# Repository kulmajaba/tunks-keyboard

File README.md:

# Tunks keyboards
> Formerly: The project that will someday be the ultimate command center upgrade

This repo contains the Tunks series keyboard schematics, born as an experiment to make a macro keyboard for editing, gaming and testing mechanical switches.

## Roadmap

Companion app: a combination of hardware and software allowing the user to control programs like Discord and OBS as well as receive visual feedback in the form of "tally lights".
Keyboard shortcuts are fragile and unpredictable, and software like AutoHotKey is considered cheating software by a lot of anti-cheat utilities, regardless of what you do with it.

**Resources**

- Discord: mute and deaf states, and setting the states instead of toggling: https://discordapp.com/developers/docs/game-sdk/discord-voice
- OBS: See which outputs are in use in the current scene (we're interested in camera, display capture and microphone), switch between scenes: https://obsproject.com/docs/
- QMK with SysEx Midi messages: https://beta.docs.qmk.fm/developing-qmk/qmk-internals-in-progress/internals_midi_device
- Keyboard PCB guide: https://wiki.ai03.com/books/pcb-design

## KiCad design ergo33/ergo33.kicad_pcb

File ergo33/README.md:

# Ergo33

A left-hand keypad with a rotary encoder for gaming, video editing, macros etc.
* 33 keys plus rotary encoder with press switch
* Kailh hot-swap sockets
* Ergonomic layout (straight columns, staggered rows)
* LED underglow and the option to add an ergo33-led-board (or any other similar external PCB) for state indicators etc.

## Notes

* The WS2812B LEDs can be configured in three different ways and you may need to change hardware or firmware config:
  * Both underglow and external board in use: Bridge the solder jumper JP1 pads 1 and 2
  * Underglow in use, no external board: reduce the number of LEDs in firmware config
  * External board in use, no underglow: Bridge the solder jumper JP1 pads 2 and 3, reduce the number of LEDs in firmware config
* Spark suppression cap C19 may be omitted or resized, may affect bootloader activation time
* The highest component on the underside of the PCB is the USB-C connector at 3,15mm
* The rotary encoder position is sized for a 30mm knob

## BOM

| Component | Value | Quantity | Example | Notes |
| --------- | ----- | -------- | ------- | ----- |
| ATmega32U4-AU TQFP-44 |  | 1 |  |  |
| Capacitor 0805 | 16pF | 2 |  | Crystal caps, size according to the crystal used |
| Capacitor 0805 | 510pF | 1 |  | Spark suppression capacitor C19 |
| Capacitor 0805 | 0.1uF | 19 |  |  |
| Capacitor 0805 | 1uF | 1 |  |  |
| Capacitor 0805 | 10uF | 2 |  |  |
| Crystal 3.2x2.5mm | 16MHz | 1 | DSX321G |  |
| Diode SOD-123 |  | 34 | 1N4148 |  |
| Fuse 1206 | 500mA | 1 | Littelfuse 1206L050/15 |  |
| Kailh Hot-swap Socket |  | 33 |  |  |
| LED WS2812B |  | 14 |  |  |
| Pin header 2.54mmx3 |  | 1 |  |  |
| Resistor 0805 | 22Ω | 2 |  |  |
| Resistor 0805 | 5.1kΩ | 2 |  |  |
| Resistor 0805 | 10kΩ | 2 |  |  |
| Rotary encoder EC11 |  | 1 |  |  |
| Switch 4x4mm SMD |  | 1 |  |  |
| USB-C 16 pin |  | 1 | HRO-TYPE-C-31-M-12 |  |
| USBLC6-2SC6 SOT-23-6 |  | 1 |  |  |
| M2 Mounting hardware |  | 12 |  |  |
| 30mm Encoder knob |  | 1 |  |  |

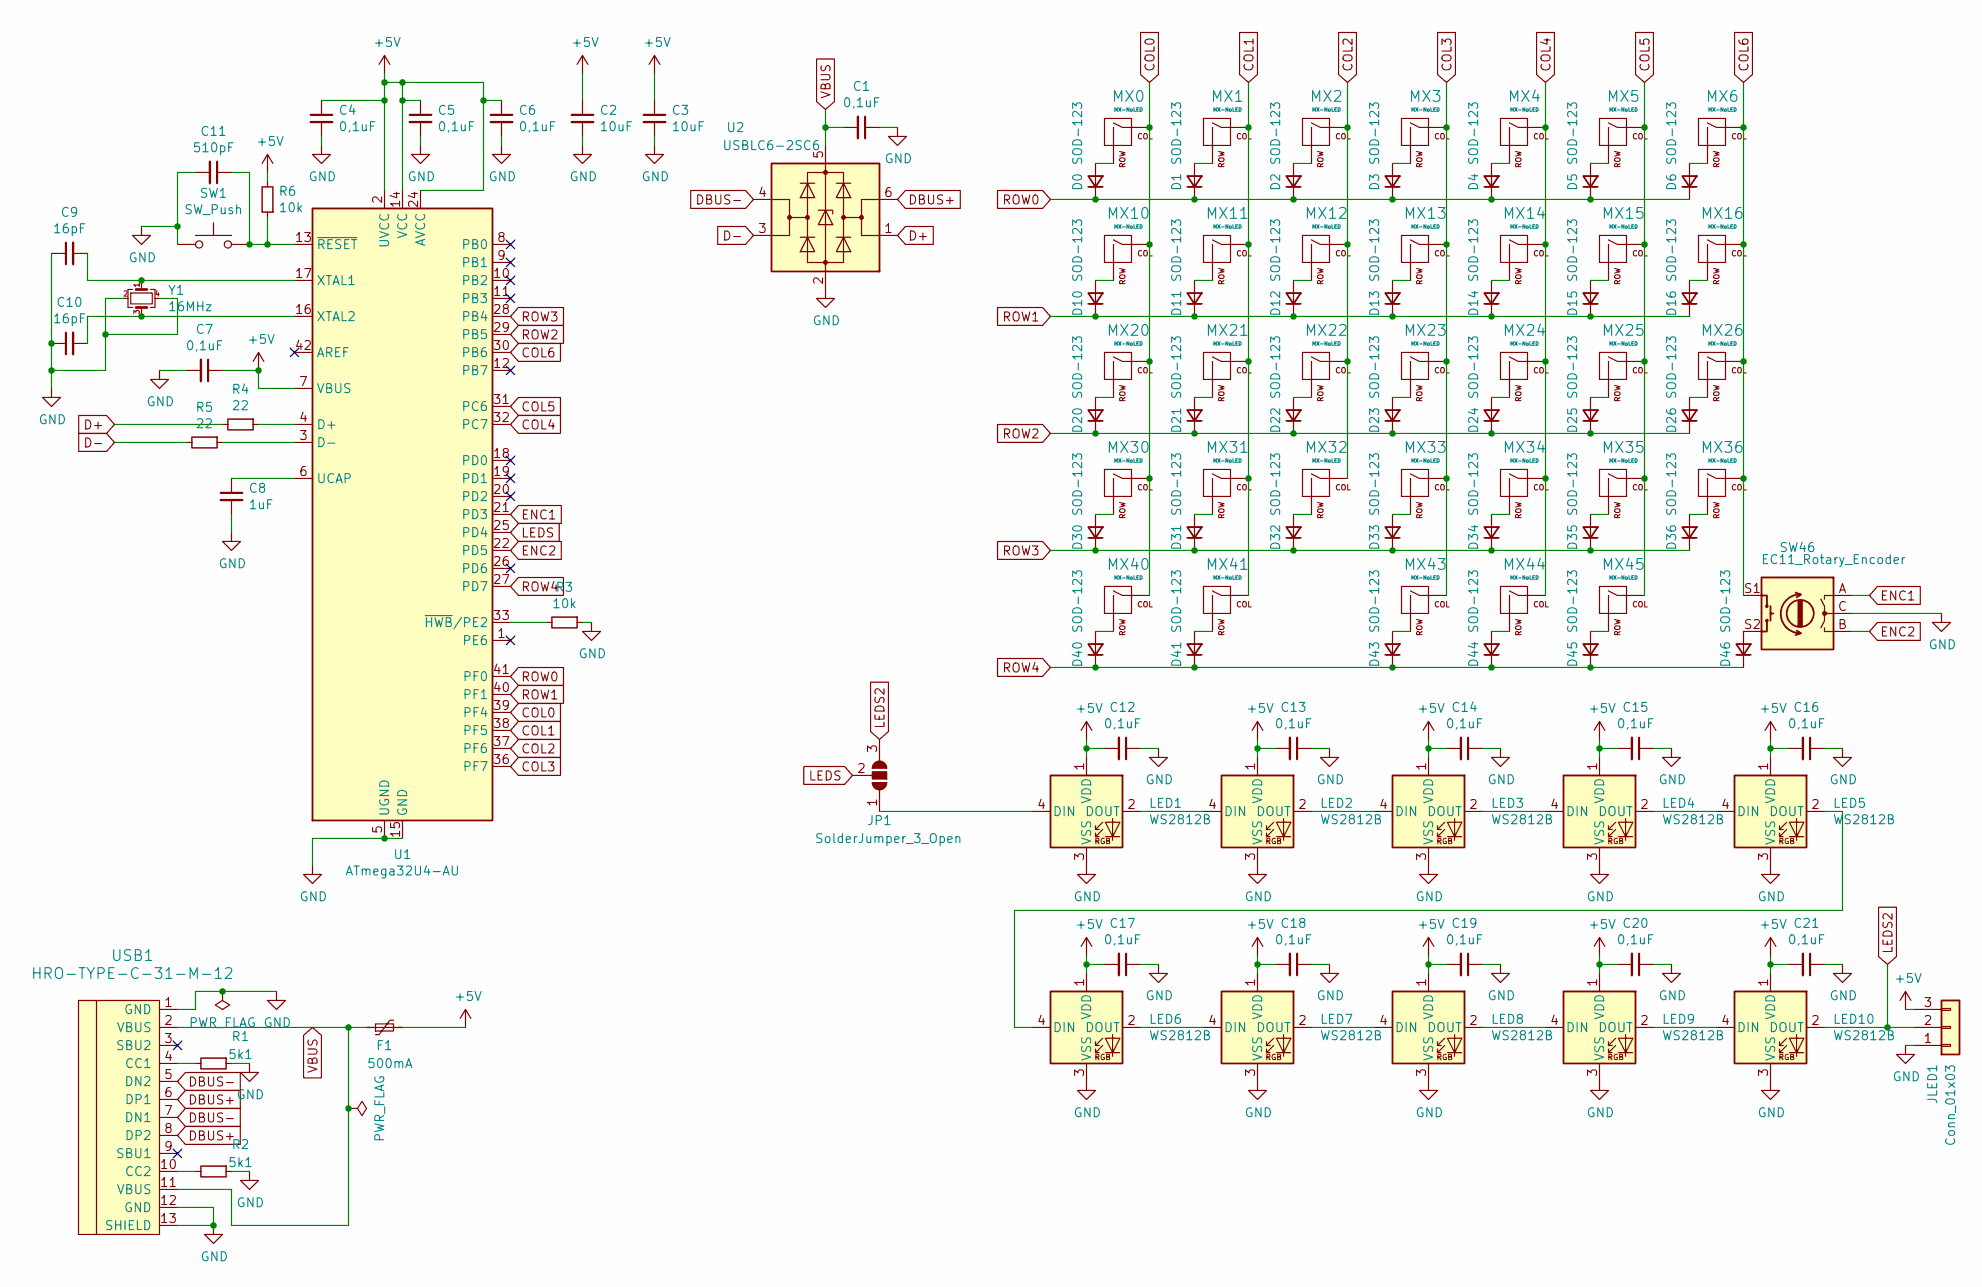
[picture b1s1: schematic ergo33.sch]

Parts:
C1, C4, C5, C6, C7, C12, C13, C14, C15, C16, C17, C18, C19, C20, C21: 0,1uF; C_0805_2012Metric_Pad1.15x1.40mm_HandSolder
C2, C3: 10uF; C_0805_2012Metric_Pad1.15x1.40mm_HandSolder
C8: 1uF; C_0805_2012Metric_Pad1.15x1.40mm_HandSolder
C9, C10: 16pF; C_0805_2012Metric_Pad1.15x1.40mm_HandSolder
C11: 510pF; C_0805_2012Metric_Pad1.15x1.40mm_HandSolder
D0, D1, D2, D3, D4, D5, D6, D10, D11, D12, D13, D14, D15, D16, D20, D21, D22, D23, D24, D25, D26, D30, D31, D32, D33, D34, D35, D36, D40, D41, D43, D44, D45, D46: SOD-123; D_SOD-123
F1: 500mA; Fuse_1206_3216Metric_Pad1.42x1.75mm_HandSolder
JLED1: Conn_01x03; PinHeader_1x03_P2.54mm_Vertical
JP1: SolderJumper_3_Open; SolderJumper-3_P1.3mm_Open_Pad1.0x1.5mm_NumberLabels
LED1, LED2, LED3, LED4, LED5, LED6, LED7, LED8, LED9, LED10: WS2812B; LED_WS2812B_PLCC4_5.0x5.0mm_P3.2mm
MX0, MX1, MX2, MX3, MX4, MX5, MX6, MX10, MX11, MX12, MX13, MX14, MX15, MX16, MX20, MX21, MX22, MX23, MX24, MX25, MX26, MX30, MX31, MX32, MX33, MX34, MX35, MX36, MX40, MX41, MX43, MX44, MX45: MX-NoLED; MXOnly-1U-Hotswap
R1, R2: 5k1; R_0805_2012Metric_Pad1.15x1.40mm_HandSolder
R3, R6: 10k; R_0805_2012Metric_Pad1.15x1.40mm_HandSolder
R4, R5: 22; R_0805_2012Metric_Pad1.15x1.40mm_HandSolder
SW1: SW_Push; SKQG-1155865
SW46: EC11_Rotary_Encoder; RotaryEncoder_Alps_EC11E-Switch_Vertical_H20mm
U1: ATmega32U4-AU; TQFP-44_10x10mm_P0.8mm
U2: USBLC6-2SC6; SOT-23-6_Handsoldering
USB1: HRO-TYPE-C-31-M-12; HRO-TYPE-C-31-M-12-HandSoldering
Y1: 16MHz; Crystal_SMD_3225-4Pin_3.2x2.5mm_HandSoldering

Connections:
+5V: C2.1, C3.1, C4.1, C5.1, C6.1, C7.1, C12.2, C13.2, C14.2, C15.2, C16.2, C17.2, C18.2, C19.2, C20.2, C21.2, F1.2, JLED1.3, LED1.1 (VDD), LED2.1 (VDD), LED3.1 (VDD), LED4.1 (VDD), LED5.1 (VDD), LED6.1 (VDD), LED7.1 (VDD), LED8.1 (VDD), LED9.1 (VDD), LED10.1 (VDD), R6.2, U1.2 (UVCC), U1.7 (VBUS), U1.14 (VCC), U1.24 (AVCC), U1.34 (VCC), U1.44 (AVCC)
COL0: MX0.1 (COL), MX10.1 (COL), MX20.1 (COL), MX30.1 (COL), MX40.1 (COL), U1.39 (PF4)
COL1: MX1.1 (COL), MX11.1 (COL), MX21.1 (COL), MX31.1 (COL), MX41.1 (COL), U1.38 (PF5)
COL2: MX2.1 (COL), MX12.1 (COL), MX22.1 (COL), MX32.1 (COL), U1.37 (PF6)
COL3: MX3.1 (COL), MX13.1 (COL), MX23.1 (COL), MX33.1 (COL), MX43.1 (COL), U1.36 (PF7)
COL4: MX4.1 (COL), MX14.1 (COL), MX24.1 (COL), MX34.1 (COL), MX44.1 (COL), U1.32 (PC7)
COL5: MX5.1 (COL), MX15.1 (COL), MX25.1 (COL), MX35.1 (COL), MX45.1 (COL), U1.31 (PC6)
COL6: MX6.1 (COL), MX16.1 (COL), MX26.1 (COL), MX36.1 (COL), SW46.S1, U1.30 (PB6)
D+: R4.2, U2.1 (I/O1)
D-: R5.2, U2.3 (I/O2)
DBUS+: U2.6 (I/O1), USB1.6 (DP1), USB1.8 (DP2)
DBUS-: U2.4 (I/O2), USB1.5 (DN2), USB1.7 (DN1)
ENC1: SW46.A, U1.21 (PD3)
ENC2: SW46.B, U1.22 (PD5)
GND: C1.1, C2.2, C3.2, C4.2, C5.2, C6.2, C7.2, C8.2, C9.1, C10.1, C11.2, C12.1, C13.1, C14.1, C15.1, C16.1, C17.1, C18.1, C19.1, C20.1, C21.1, JLED1.1, LED1.3 (VSS), LED2.3 (VSS), LED3.3 (VSS), LED4.3 (VSS), LED5.3 (VSS), LED6.3 (VSS), LED7.3 (VSS), LED8.3 (VSS), LED9.3 (VSS), LED10.3 (VSS), R1.1, R2.1, R3.1, SW1.1, SW46.C, U1.5 (UGND), U1.15 (GND), U1.23 (GND), U1.35 (GND), U1.43 (GND), U2.2 (GND), USB1.1 (GND), USB1.12 (GND), USB1.13 (SHIELD), Y1.2, Y1.4
LEDS: JP1.2 (C), U1.25 (PD4)
LEDS2: JLED1.2, JP1.3 (B), LED10.2 (DOUT)
unnamed: C8.1, U1.6 (UCAP)
unnamed: C9.2, U1.17 (XTAL1), Y1.1
unnamed: C10.2, U1.16 (XTAL2), Y1.3
unnamed: C11.1, R6.1, SW1.2, U1.13 (~RESET)
unnamed: D0.2 (A), MX0.2 (ROW)
unnamed: D1.2 (A), MX1.2 (ROW)
unnamed: D2.2 (A), MX2.2 (ROW)
unnamed: D3.2 (A), MX3.2 (ROW)
unnamed: D4.2 (A), MX4.2 (ROW)
unnamed: D5.2 (A), MX5.2 (ROW)
unnamed: D6.2 (A), MX6.2 (ROW)
unnamed: D10.2 (A), MX10.2 (ROW)
unnamed: D11.2 (A), MX11.2 (ROW)
unnamed: D12.2 (A), MX12.2 (ROW)
unnamed: D13.2 (A), MX13.2 (ROW)
unnamed: D14.2 (A), MX14.2 (ROW)
unnamed: D15.2 (A), MX15.2 (ROW)
unnamed: D16.2 (A), MX16.2 (ROW)
unnamed: D20.2 (A), MX20.2 (ROW)
unnamed: D21.2 (A), MX21.2 (ROW)
unnamed: D22.2 (A), MX22.2 (ROW)
unnamed: D23.2 (A), MX23.2 (ROW)
unnamed: D24.2 (A), MX24.2 (ROW)
unnamed: D25.2 (A), MX25.2 (ROW)
unnamed: D26.2 (A), MX26.2 (ROW)
unnamed: D30.2 (A), MX30.2 (ROW)
unnamed: D31.2 (A), MX31.2 (ROW)
unnamed: D32.2 (A), MX32.2 (ROW)
unnamed: D33.2 (A), MX33.2 (ROW)
unnamed: D34.2 (A), MX34.2 (ROW)
unnamed: D35.2 (A), MX35.2 (ROW)
unnamed: D36.2 (A), MX36.2 (ROW)
unnamed: D40.2 (A), MX40.2 (ROW)
unnamed: D41.2 (A), MX41.2 (ROW)
unnamed: D43.2 (A), MX43.2 (ROW)
unnamed: D44.2 (A), MX44.2 (ROW)
unnamed: D45.2 (A), MX45.2 (ROW)
unnamed: D46.2 (A), SW46.S2
unnamed: JP1.1 (A), LED1.4 (DIN)
unnamed: LED1.2 (DOUT), LED2.4 (DIN)
unnamed: LED2.2 (DOUT), LED3.4 (DIN)
unnamed: LED3.2 (DOUT), LED4.4 (DIN)
unnamed: LED4.2 (DOUT), LED5.4 (DIN)
unnamed: LED5.2 (DOUT), LED6.4 (DIN)
unnamed: LED6.2 (DOUT), LED7.4 (DIN)
unnamed: LED7.2 (DOUT), LED8.4 (DIN)
unnamed: LED8.2 (DOUT), LED9.4 (DIN)
unnamed: LED9.2 (DOUT), LED10.4 (DIN)
unnamed: R1.2, USB1.4 (CC1)
unnamed: R2.2, USB1.10 (CC2)
unnamed: R3.2, U1.33 (~HWB~/PE2)
unnamed: R4.1, U1.4 (D+)
unnamed: R5.1, U1.3 (D-)
ROW0: D0.1 (K), D1.1 (K), D2.1 (K), D3.1 (K), D4.1 (K), D5.1 (K), D6.1 (K), U1.41 (PF0)
ROW1: D10.1 (K), D11.1 (K), D12.1 (K), D13.1 (K), D14.1 (K), D15.1 (K), D16.1 (K), U1.40 (PF1)
ROW2: D20.1 (K), D21.1 (K), D22.1 (K), D23.1 (K), D24.1 (K), D25.1 (K), D26.1 (K), U1.29 (PB5)
ROW3: D30.1 (K), D31.1 (K), D32.1 (K), D33.1 (K), D34.1 (K), D35.1 (K), D36.1 (K), U1.28 (PB4)
ROW4: D40.1 (K), D41.1 (K), D43.1 (K), D44.1 (K), D45.1 (K), D46.1 (K), U1.27 (PD7)
VBUS: C1.2, F1.1, U2.5 (VBUS), USB1.2 (VBUS), USB1.11 (VBUS)

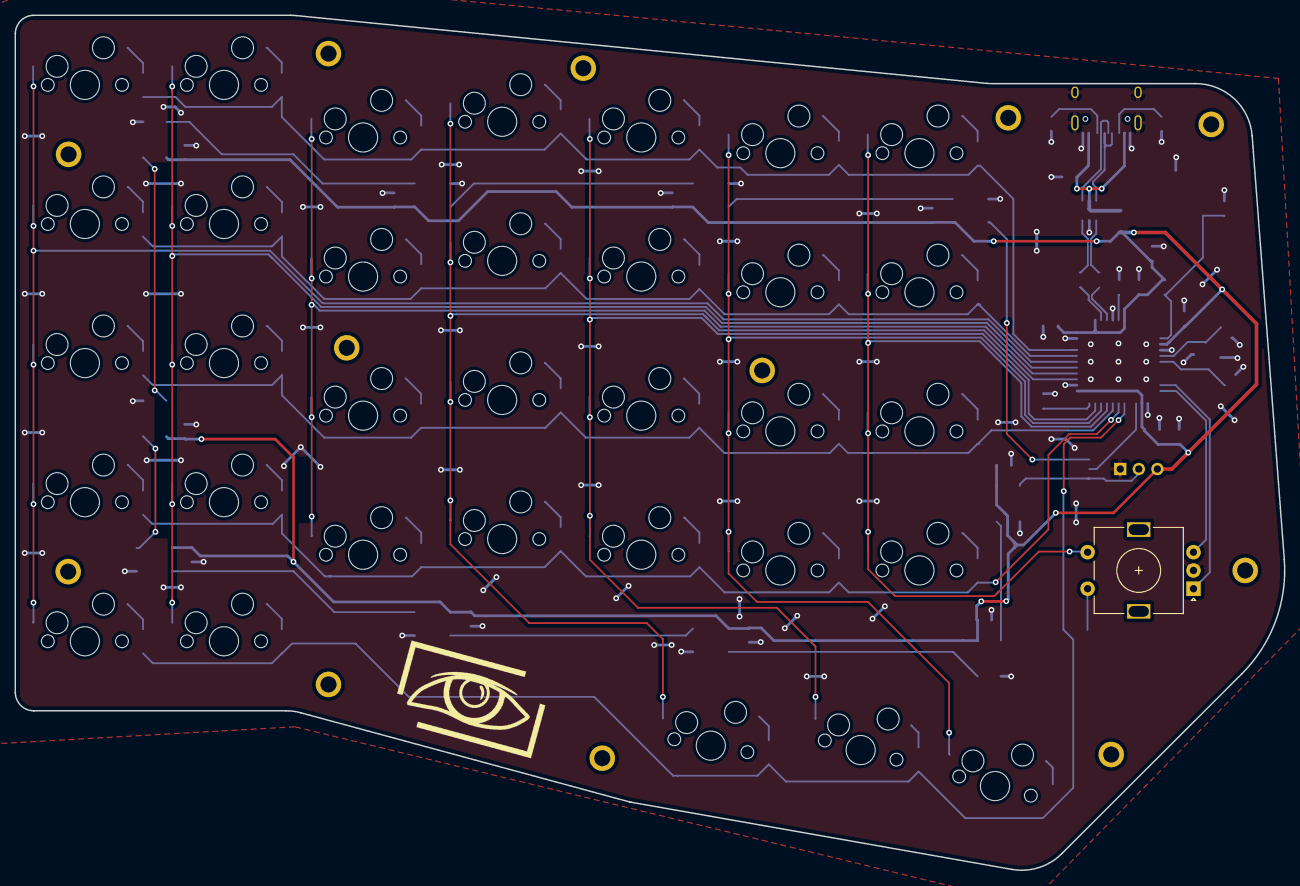
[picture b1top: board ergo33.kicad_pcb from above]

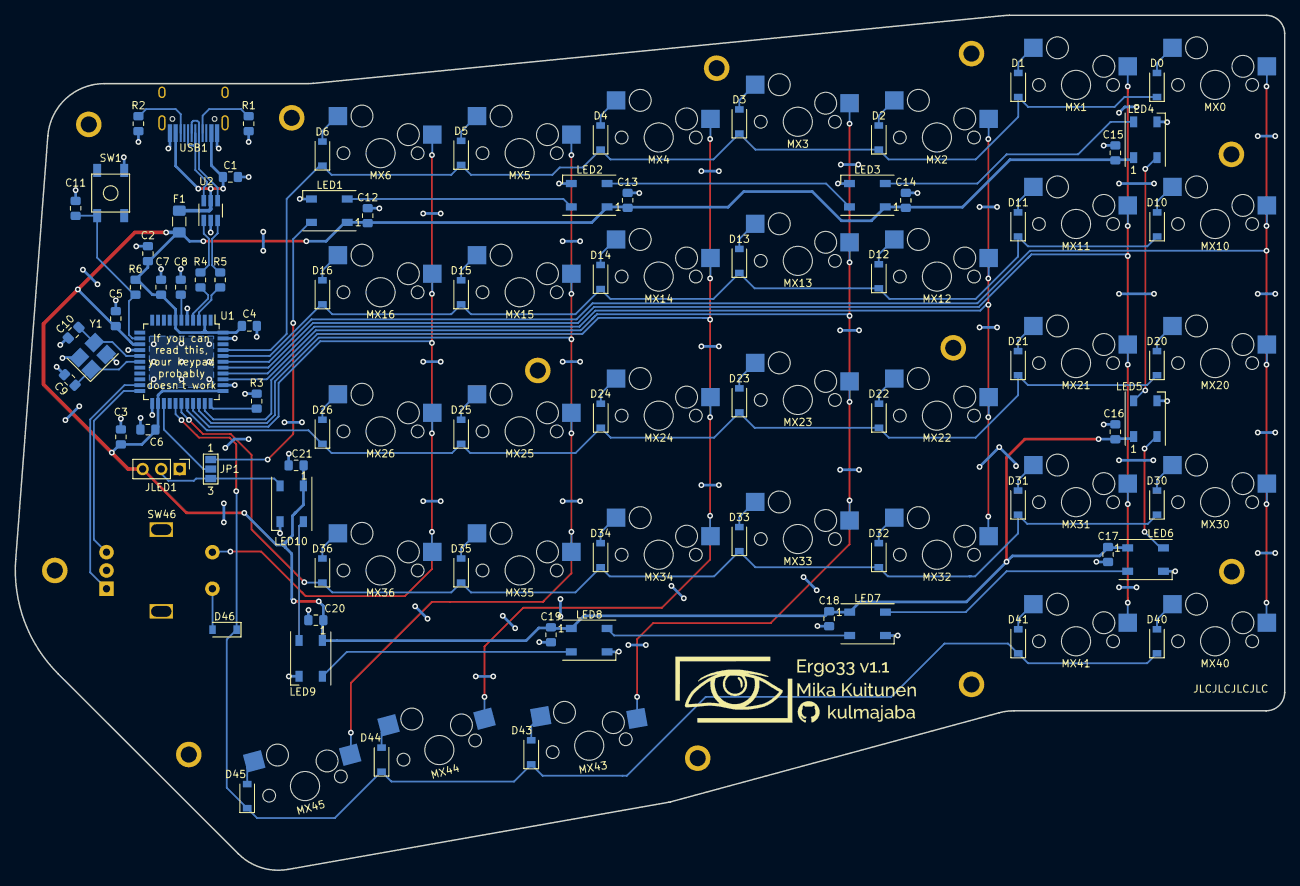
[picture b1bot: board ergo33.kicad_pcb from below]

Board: 2 copper layers, 173.8 x 117.1 mm, 113 parts (79 on the bottom side), 76 nets.

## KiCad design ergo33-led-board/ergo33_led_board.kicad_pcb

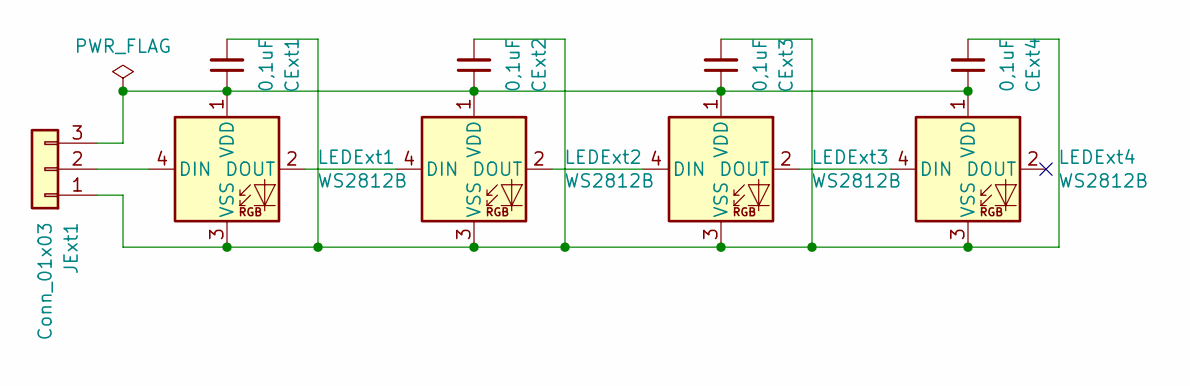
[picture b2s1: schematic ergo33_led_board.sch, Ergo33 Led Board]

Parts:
CExt1, CExt2, CExt3, CExt4: 0,1uF; C_0805_2012Metric_Pad1.15x1.40mm_HandSolder
JExt1: Conn_01x03; PinHeader_1x03_P2.54mm_Vertical
LEDExt1, LEDExt2, LEDExt3, LEDExt4: WS2812B; LED_WS2812B_PLCC4_5.0x5.0mm_P3.2mm

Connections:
unnamed: CExt1.1, CExt2.1, CExt3.1, CExt4.1, JExt1.3, LEDExt1.1 (VDD), LEDExt2.1 (VDD), LEDExt3.1 (VDD), LEDExt4.1 (VDD)
unnamed: CExt1.2, CExt2.2, CExt3.2, CExt4.2, JExt1.1, LEDExt1.3 (VSS), LEDExt2.3 (VSS), LEDExt3.3 (VSS), LEDExt4.3 (VSS)
unnamed: JExt1.2, LEDExt1.4 (DIN)
unnamed: LEDExt1.2 (DOUT), LEDExt2.4 (DIN)
unnamed: LEDExt2.2 (DOUT), LEDExt3.4 (DIN)
unnamed: LEDExt3.2 (DOUT), LEDExt4.4 (DIN)

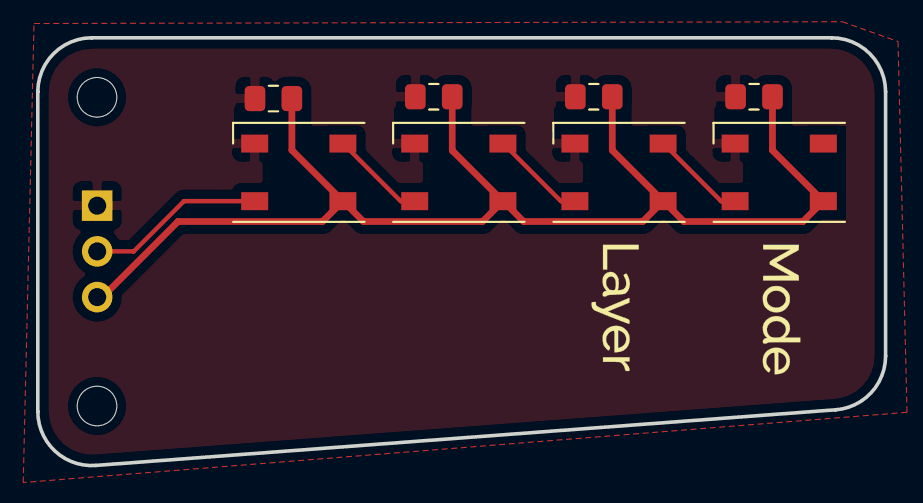
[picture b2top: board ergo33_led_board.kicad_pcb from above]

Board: 2 copper layers, 47.1 x 23.8 mm, 11 parts (1 on the bottom side), 6 nets.

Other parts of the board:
M1, M2: MountingHole_2.2mm_M2_ISO7380

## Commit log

2020-07-19 Add submodules
2020-07-19 Add ergo33 base
2020-07-20 Add Ergo33 schema
2020-07-20 Update Ergo33
2020-07-23 Start trace layout
2020-07-23 Rerouting ergo33
2020-07-23 Finish ergo33 routing v1
2020-07-23 Fix ergo33 routing
2020-07-24 Add arc suppression cap to ergo33
2020-07-24 Reroute ergo33 MCU area
2020-07-24 Minor routing fix to ergo33
2020-07-24 ergo33 minor fixes
2020-07-24 Fix DRC errors
2020-07-24 ergo33: Change USB connectors and add ESD protection
2020-07-24 Add mounting holes and tweak silkscreen
2020-07-24 ergo33: footprint changes
2020-07-24 ergo33: fix a derp
2020-07-24 Add external light PCB
2020-07-24 ergo33: minor cleanup
2020-07-24 ergo33: minor tweaking
2020-07-24 ergo33: Panelize maybe?
2020-07-25 Ergo33: add graphics
2020-07-25 Ergo33: archive footprints
2020-07-25 Ergo33: refill ground
2020-07-25 Ergo33: depanelize :(
2020-07-25 Ergo33: generate gerbers
2020-07-25 Ergo33: update LED PCB gerbers
2020-07-27 Change a few cap values
2020-08-03 Ergo33: rev2
2020-08-03 Ergo33: Change logo to v1.1
2020-09-30 Add Readme and BOM for Ergo33
2020-10-16 Add Ergo33 prpro keboard shortcut map for Premiere Pro
2022-03-09 Create LICENSE
